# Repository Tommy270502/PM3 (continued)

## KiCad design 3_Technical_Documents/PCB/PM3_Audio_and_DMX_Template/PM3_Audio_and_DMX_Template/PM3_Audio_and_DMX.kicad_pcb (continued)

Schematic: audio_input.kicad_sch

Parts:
C42, C43: 10u; CP_Elec_4x5.8; MPN EEE1HA010SR
C44, C45: 470p; C_0603_1608Metric; MPN GPC0603103
C46, C47: 2n7 COG/X7R; C_0603_1608Metric; MPN GPC0603103
C48, C49: 100n; C_0603_1608Metric; MPN GPC0603104-X7R
R37, R38: 10k; R_0603_1608Metric; MPN GPR060310K
R39, R40: 634R; R_0603_1608Metric; MPN GPR060310K
R41, R42: 91R; R_0603_1608Metric; MPN GPR060310K
U11: OPA2134; SOIC-8_3.9x4.9mm_P1.27mm; MPN OPA2134UA
U12: OPA2134; SOIC-8_3.9x4.9mm_P1.27mm

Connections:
/PM3 Audio/Codec with analog line buffers/Audio Input/AINA: C46.1, R39.2, R41.2; also elsewhere on the board
/PM3 Audio/Codec with analog line buffers/Audio Input/AINB: C47.2, R40.2, R42.2; also elsewhere on the board
/PM3 Audio/Codec with analog line buffers/LINE_IN_L: C42.2; also elsewhere on the board
/PM3 Audio/Codec with analog line buffers/LINE_IN_R: C43.2; also elsewhere on the board
GND: C48.2, C49.2, U11.4 (V-), U12.4 (V-); also elsewhere on the board
unnamed: C44.1, R41.1, U11.1
unnamed: C45.1, R42.1, U11.7
unnamed: C42.1, R37.2, U11.3 (+)
unnamed: C44.2, R39.1, U11.2 (-)
unnamed: C43.1, R38.1, U11.5 (+)
unnamed: C45.2, R40.1, U11.6 (-)
unnamed: U12.6 (-), U12.7
VA: C48.1, C49.1, U11.8 (V+), U12.8 (V+); also elsewhere on the board
VCOM: C46.2, C47.1, R37.1, R38.2, U12.1, U12.2 (-), U12.3 (+), U12.5 (+); also elsewhere on the board

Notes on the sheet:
Analog Input

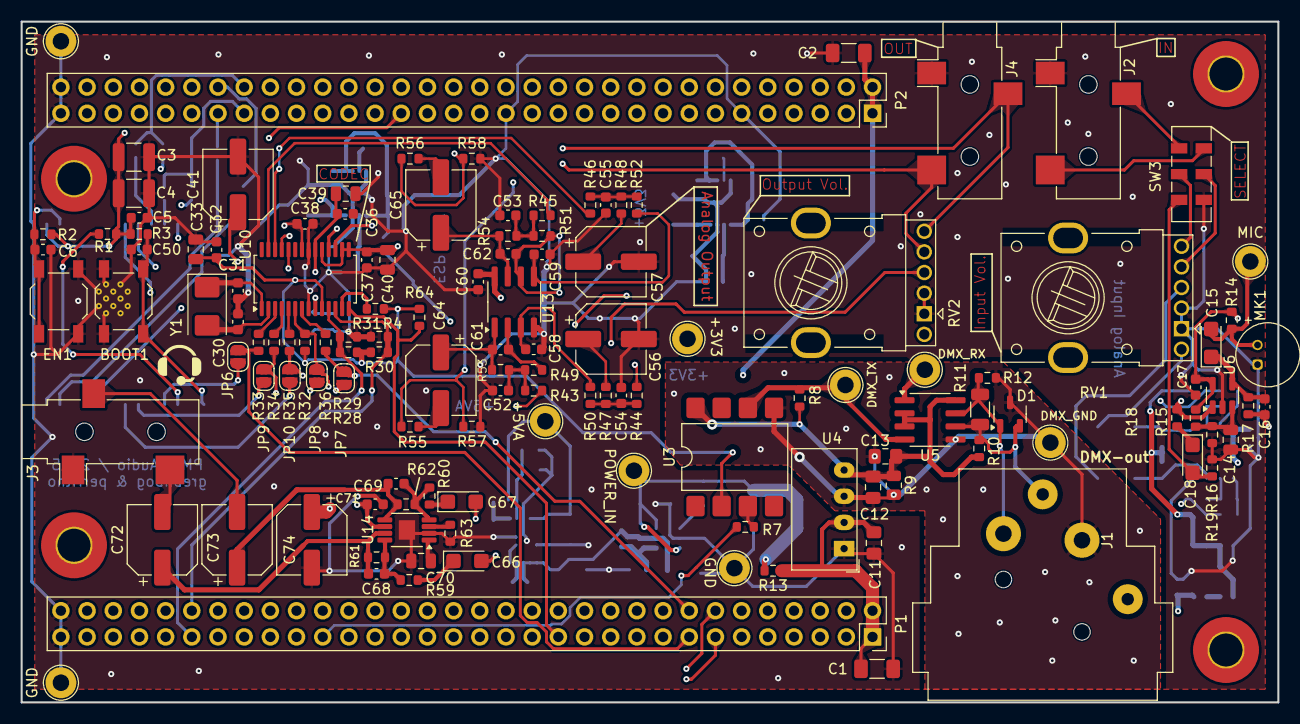
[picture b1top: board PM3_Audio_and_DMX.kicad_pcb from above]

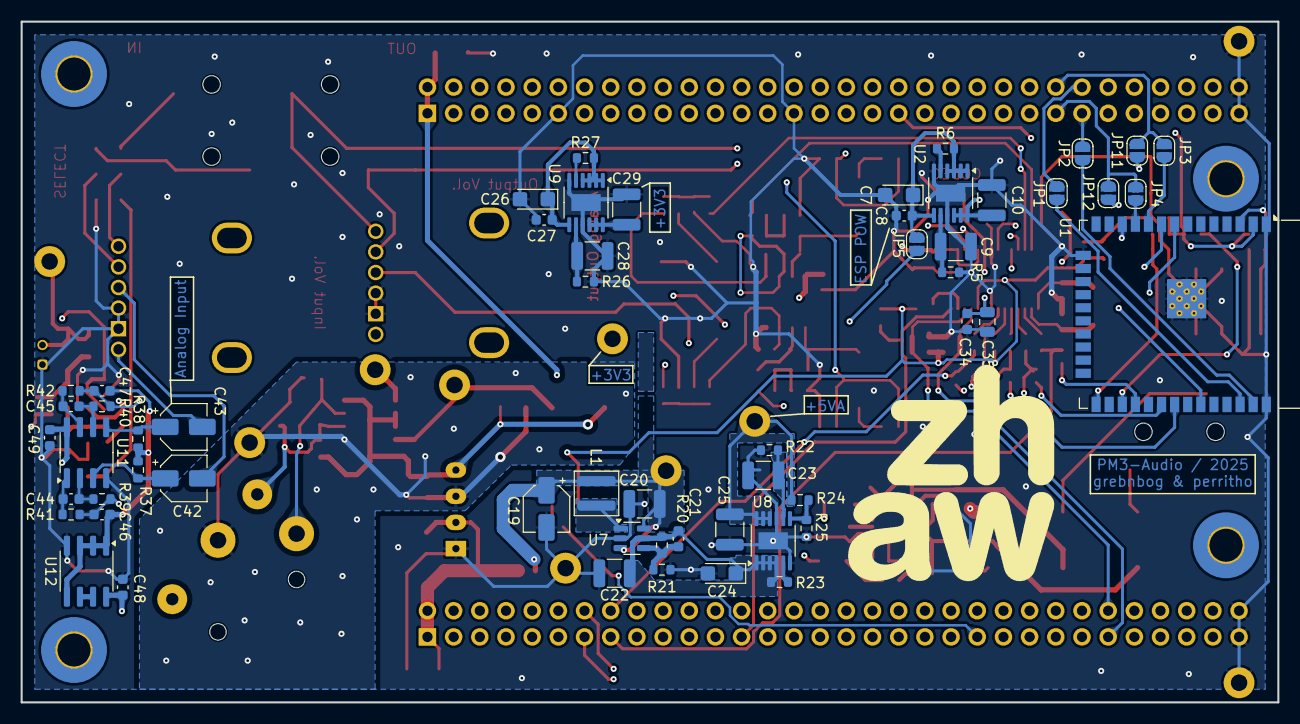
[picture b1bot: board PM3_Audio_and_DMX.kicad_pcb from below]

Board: 4 copper layers, 121.9 x 66.0 mm, 191 parts (56 on the bottom side), 116 nets.

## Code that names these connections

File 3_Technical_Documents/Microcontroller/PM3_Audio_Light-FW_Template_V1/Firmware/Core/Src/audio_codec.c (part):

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
/* ============================================================
* CONTROL GPIOs
*  - PB4: codec reset (used by codec_reset())
* ============================================================ */

// --- GPIOB: PB4 as Output, initial Low (hold codec in reset) ---
GPIO_InitStruct.Pin   = GPIO_PIN_4;
GPIO_InitStruct.Mode  = GPIO_MODE_OUTPUT_PP;
GPIO_InitStruct.Pull  = GPIO_NOPULL;
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HAL_GPIO_WritePin(GPIOB, GPIO_PIN_4, GPIO_PIN_RESET);

/* ============================================================
* SAI1 PINS (PE2..PE6) FOR CODEC
*
*  PE2 : SAI1_MCLK_A → CS4271 MCLK
*  PE3 : SAI1_SD_B   → Codec SDIN  (STM -> codec)
*  PE4 : SAI1_FS_A   → Codec LRCK
*  PE5 : SAI1_SCK_A  → Codec SCLK/BCLK
*  PE6 : SAI1_SD_A   → Codec SDOUT (codec -> STM)
*
* All must be AF6 for SAI1.
* ============================================================ */
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     * SAI1 BLOCK A
     * ------------------------------------------------------------
     * Always configure Block A as a slave receiver so that:
     *  - FS_A / SCK_A (PE4 / PE5) are used as the frame/bit clock,
     *  - Block B can be synchronous to Block A and share these clocks.
     * In AUDIO_INPUT_I2S mode we simply DON'T use DMA on Block A.
     * ============================================================ */
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     * SAI1 BLOCK B
     * ------------------------------------------------------------
     * Slave transmitter, **synchronous to Block A** so it uses
     * the same FS_A/SCK_A (PE4/PE5) clocks from the CS4271 (master).
     * ============================================================ */
    SAI1_Block_B->CR1 &= ~SAI_xCR1_SAIEN;   // Disable before config

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
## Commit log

2025-10-03 migrated project
2025-10-03 added up do date documents for week 3
2025-10-03 Gant chart update
2025-10-03 new push
2025-10-03 ltspice simulation
2025-10-03 codec and layout
2025-10-04 i2s added
2025-10-06 pdf schematics and minor visual improvements
2025-10-09 FW_Template
2025-10-09 gitignore update (+ unnecessary files removed)
2025-10-09 rework esp32, codec and layout
2025-10-09 more layout
2025-10-10 updated capacitors
2025-10-10 minor modifications to esp32 bootmodes
2025-10-11 esp-stm connection (+ conflict recolution)
2025-10-13 layout complete
2025-10-13 layout fix
2025-10-13 added 3d models
2025-10-13 finalized design and generated gerber
2025-10-13 made a zip
2025-10-14 Amutec und Bmutec left floating
2025-10-14 reqorked pcb
2025-10-14 final design
2025-10-14 added updated gerber/drill files
2025-10-14 old gerber zip removed
2025-10-15 fixed pcb, again.
2025-10-15 finalized hardware
2025-10-15 final final
2025-10-15 deleted build artifacts
2025-10-15 updated and restructured gitignore files
2025-10-15 resolved todo's in audio_codec
2025-10-17 starting HW testing document
2025-10-17 forgot programming pins txd rxd esp32
2025-10-17 worked on test cases and added current consumption sheet
2025-10-17 stm: scrollable menu
2025-10-17 CubeIDE settings
2025-10-18 added esp32 firmware template
2025-10-24 added new document versions
2025-10-24 interactive bom
2025-10-25 updated measurement table template
2025-10-25 schematics, layout and bom updated (to match corrections)
2025-11-07 comments in schematics
2025-11-07 hw testing (wip)
2025-11-07 setup environment on new laptop successfull build of project for esp32
2025-11-07 hw report updated + gitignore
2025-11-07 removed build files
2025-11-08 hw report wip
2025-11-08 hw report some more wip
2025-11-13 simulation updated to match new resistor values
2025-11-14 PCB fixes image
2025-11-14 hw report - done
2025-11-14 testing report - done
2025-11-14 testing report PDF
2025-11-16 added frequency sweep description and also pictures for the modifications carried out to pcb
2025-11-21 new timeline version, old versions removed
2025-11-21 test report file renamed
2025-11-21 HW report and related files
2025-11-28 implement standalone code-esp
2025-11-28 new architexture esp-stm
2025-11-28 mono-stereo switching
2025-12-04 add over the air updates esp32
2025-12-04 combined OTA with BT sink and I2C over to STM32
2025-12-04 stm32 recieve i2s from esp32
2025-12-04 gitignore updated
2025-12-05 presentation guidlines added
2025-12-05 checklist mark document updated
2025-12-05 graded excel test report added
2025-12-10 worked on esp32-stm32-codec
2025-12-11 graded hw report (language)
2025-12-11 dmx set colors
2025-12-12 color control
2025-12-12 added low pass filter
2025-12-12 effect active screen
2025-12-12 effect active fix
2025-12-12 effect active ui
2025-12-12 added filters
2025-12-12 update output buffer
2025-12-12 removed .launch file + gitignore update
2025-12-13 FW block diagram
2025-12-19 multiple filters added and menu apdated accordingly
2025-12-19 Refactor menu info screen
2026-01-21 block diagram improved
2026-01-21 presentation started
2026-01-21 finished powerpoint
2026-01-22 photos in presentation
